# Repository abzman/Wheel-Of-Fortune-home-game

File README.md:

# Wheel-Of-Fortune-home-game
information about the reverse engineering of the wheel of fortune home electronic game

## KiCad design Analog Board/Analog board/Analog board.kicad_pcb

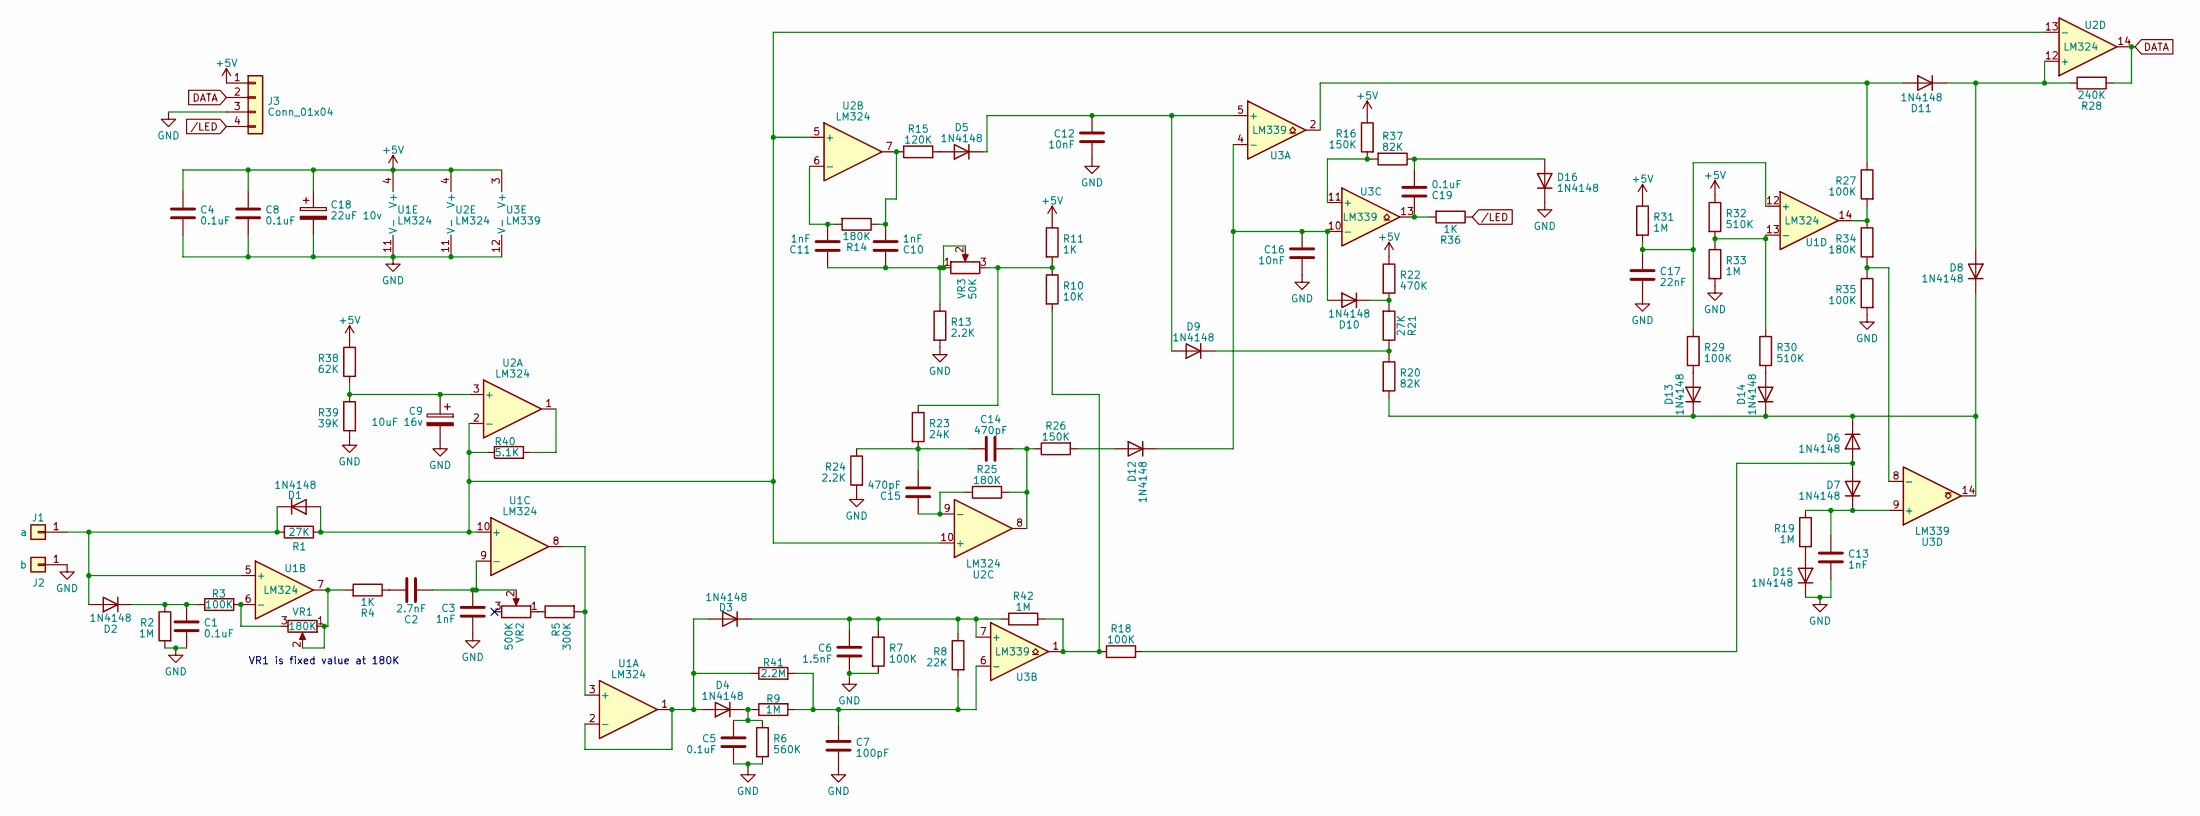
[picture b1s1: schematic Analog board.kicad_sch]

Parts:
C1, C4, C5, C8, C19: 0.1uF; C_Disc_D4.7mm_W2.5mm_P5.00mm
C2: 2.7nF; C_Disc_D4.7mm_W2.5mm_P5.00mm
C3, C10, C11, C13: 1nF; C_Disc_D4.7mm_W2.5mm_P5.00mm
C6: 1.5nF; C_Disc_D4.7mm_W2.5mm_P5.00mm
C7: 100pF; C_Disc_D4.7mm_W2.5mm_P5.00mm
C9: 10uF 16v; CP_Radial_D5.0mm_P2.50mm
C12, C16: 10nF; C_Disc_D4.7mm_W2.5mm_P5.00mm
C14, C15: 470pF; C_Disc_D4.7mm_W2.5mm_P5.00mm
C17: 22nF; C_Disc_D4.7mm_W2.5mm_P5.00mm
C18: 22uF 10v; CP_Radial_D5.0mm_P2.50mm
D1, D2, D3, D4, D5, D6, D7, D8, D9, D10, D11, D12, D13, D14, D15, D16: 1N4148; D_DO-35_SOD27_P10.16mm_Horizontal
J1: a; PinHeader_1x01_P2.54mm_Vertical
J2: b; PinHeader_1x01_P2.54mm_Vertical
J3: Conn_01x04; PinHeader_2x02_P2.54mm_Vertical
R1, R21: 27K; R_Axial_DIN0207_L6.3mm_D2.5mm_P10.16mm_Horizontal
R2, R9, R19, R31, R33, R42: 1M; R_Axial_DIN0207_L6.3mm_D2.5mm_P10.16mm_Horizontal
R3, R7, R18, R27, R29, R35: 100K; R_Axial_DIN0207_L6.3mm_D2.5mm_P10.16mm_Horizontal
R4, R11, R36: 1K; R_Axial_DIN0207_L6.3mm_D2.5mm_P10.16mm_Horizontal
R5: 300K; R_Axial_DIN0207_L6.3mm_D2.5mm_P10.16mm_Horizontal
R6: 560K; R_Axial_DIN0207_L6.3mm_D2.5mm_P10.16mm_Horizontal
R8: 22K; R_Axial_DIN0207_L6.3mm_D2.5mm_P10.16mm_Horizontal
R10: 10K; R_Axial_DIN0207_L6.3mm_D2.5mm_P10.16mm_Horizontal
R13, R24: 2.2K; R_Axial_DIN0207_L6.3mm_D2.5mm_P10.16mm_Horizontal
R14, R25, R34: 180K; R_Axial_DIN0207_L6.3mm_D2.5mm_P10.16mm_Horizontal
R15: 120K; R_Axial_DIN0207_L6.3mm_D2.5mm_P10.16mm_Horizontal
R16, R26: 150K; R_Axial_DIN0207_L6.3mm_D2.5mm_P10.16mm_Horizontal
R20, R37: 82K; R_Axial_DIN0207_L6.3mm_D2.5mm_P10.16mm_Horizontal
R22: 470K; R_Axial_DIN0207_L6.3mm_D2.5mm_P10.16mm_Horizontal
R23: 24K; R_Axial_DIN0207_L6.3mm_D2.5mm_P10.16mm_Horizontal
R28: 240K; R_Axial_DIN0207_L6.3mm_D2.5mm_P10.16mm_Horizontal
R30, R32: 510K; R_Axial_DIN0207_L6.3mm_D2.5mm_P10.16mm_Horizontal
R38: 62K; R_Axial_DIN0207_L6.3mm_D2.5mm_P10.16mm_Horizontal
R39: 39K; R_Axial_DIN0207_L6.3mm_D2.5mm_P10.16mm_Horizontal
R40: 5.1K; R_Axial_DIN0207_L6.3mm_D2.5mm_P10.16mm_Horizontal
R41: 2.2M; R_Axial_DIN0207_L6.3mm_D2.5mm_P10.16mm_Horizontal
U1, U2: LM324; DIP-14_W7.62mm
U3: LM339; DIP-14_W7.62mm
VR1: 180K; Potentiometer_ACP_CA9-V10_Vertical
VR2: 500K; Potentiometer_ACP_CA9-V10_Vertical
VR3: 50K; Potentiometer_ACP_CA9-V10_Vertical

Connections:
+5V: C4.1, C8.1, C18.1, J3.1, R11.1, R16.1, R22.1, R31.1, R32.1, R38.1, U1.4 (V+), U2.4 (V+), U3.3 (V+)
DATA: J3.2, R28.2, U2.14
GND: C1.2, C3.2, C4.2, C5.2, C6.2, C7.2, C8.2, C9.2, C12.2, C13.2, C16.2, C17.2, C18.2, D15.1 (K), D16.1 (K), J2.1, J3.3, R2.2, R6.2, R7.2, R13.2, R24.2, R33.2, R35.2, R39.2, U1.11 (V-), U2.11 (V-), U3.12 (V-)
unnamed: C2.1, R4.1
unnamed: C10.1, C11.1, R13.1, VR3.1, VR3.2
unnamed: C10.2, R14.1, R15.1, U2.7
unnamed: C14.1, C15.2, R23.2, R24.1
unnamed: C14.2, R25.1, R26.1, U2.8
unnamed: C19.1, R36.2, U3.13
unnamed: D1.2 (A), R1.1, R40.1, U1.10 (+), U2.2 (-), U2.5 (+), U2.10 (+), U2.13 (-)
unnamed: D1.1 (K), D2.2 (A), J1.1, R1.2, U1.5 (+)
unnamed: C1.1, D2.1 (K), R2.1, R3.1
unnamed: D3.2 (A), D4.2 (A), R41.1, U1.1, U1.2 (-)
unnamed: C6.1, D3.1 (K), R7.1, R8.1, R42.1, U3.7 (+)
unnamed: C5.1, D4.1 (K), R6.1, R9.1
unnamed: D5.2 (A), R15.2
unnamed: C12.1, D5.1 (K), D9.2 (A), U3.5 (+)
unnamed: D6.2 (A), D7.2 (A), R18.2
unnamed: C13.1, D7.1 (K), R19.1, U3.9 (+)
unnamed: D9.1 (K), R20.1, R21.1
unnamed: C16.1, D10.2 (A), D12.1 (K), U3.4 (-), U3.10 (-)
unnamed: D10.1 (K), R21.2, R22.2
unnamed: D11.2 (A), R27.1, U3.2
unnamed: D8.2 (A), D11.1 (K), R28.1, U2.12 (+)
unnamed: D12.2 (A), R26.2
unnamed: D13.2 (A), R29.2
unnamed: D6.1 (K), D8.1 (K), D13.1 (K), D14.1 (K), R20.2, U3.14
unnamed: D14.2 (A), R30.2
unnamed: D15.2 (A), R19.2
unnamed: C19.2, D16.2 (A), R37.1
unnamed: R4.2, U1.7, VR1.1, VR1.2
unnamed: R10.1, R11.2, R23.1, VR3.3
unnamed: R10.2, R18.1, R42.2, U3.1
unnamed: R27.2, R34.1, U1.14
unnamed: R40.2, U2.1
unnamed: R5.2, U1.3 (+), U1.8
unnamed: R3.2, U1.6 (-), VR1.3
unnamed: C2.2, C3.1, U1.9 (-), VR2.2
unnamed: C17.1, R29.1, R31.2, U1.12 (+)
unnamed: R30.1, R32.2, R33.1, U1.13 (-)
unnamed: C9.1, R38.2, R39.1, U2.3 (+)
unnamed: C11.2, R14.2, U2.6 (-)
unnamed: C15.1, R25.2, U2.9 (-)
unnamed: C7.1, R8.2, R9.2, R41.2, U3.6 (-)
unnamed: R16.2, R37.2, U3.11 (+)
unnamed: R34.2, R35.1, U3.8 (-)
/LED: J3.4, R36.1

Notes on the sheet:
VR1 is fixed value at 180K

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
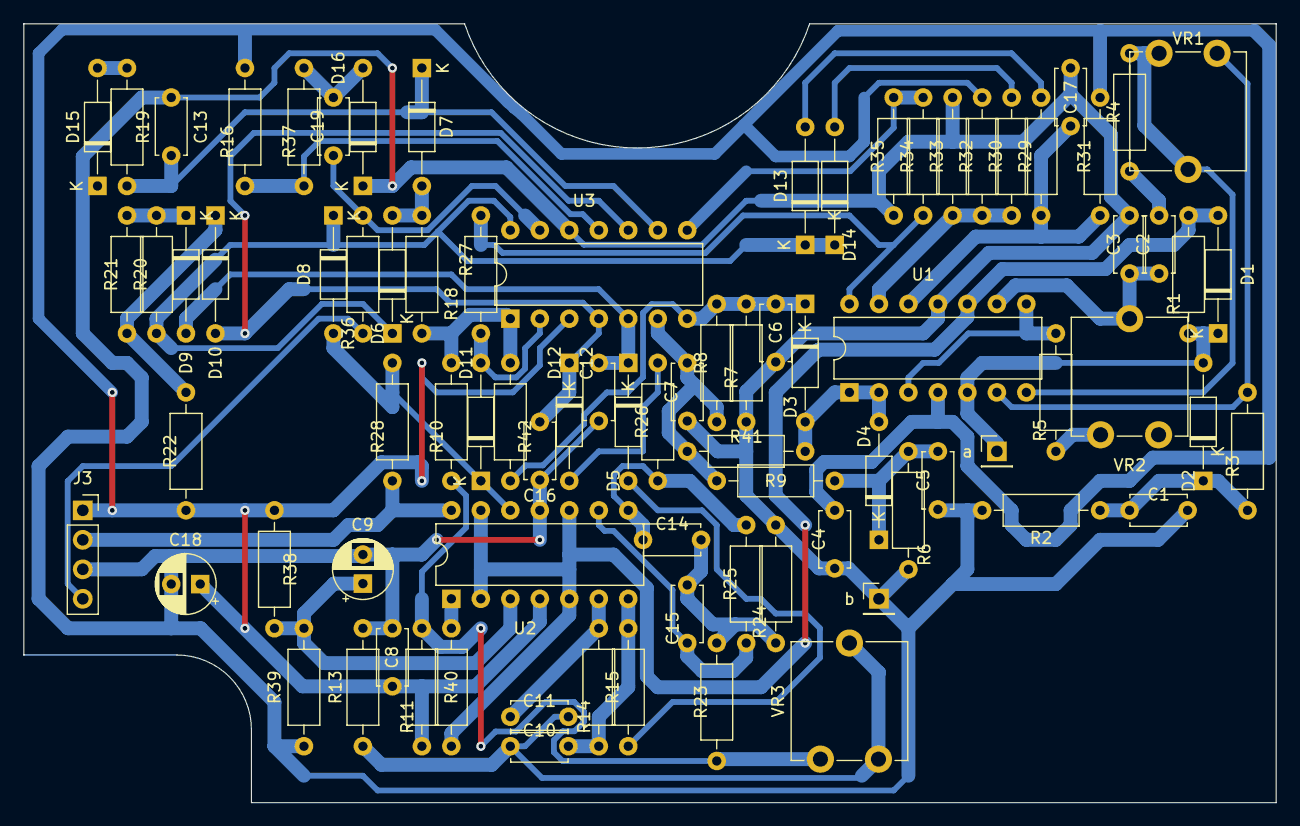
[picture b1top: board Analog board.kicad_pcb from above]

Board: 2 copper layers, 107.9 x 67.1 mm, 84 parts (0 on the bottom side), 48 nets.

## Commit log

2023-06-19 reference photos and initial layout (partial)
2023-06-20 finished messy layout
2023-06-20 better layout
2023-06-24 finished rough layout
2024-01-18 added images
